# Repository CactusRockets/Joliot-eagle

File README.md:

# Avionics Boards for the Joliot Rocket

This repository contains the design files for the avionics boards used in the **Joliot rocket** developed by **Cactus Rockets Design**.

### Description

The avionics system is composed of the following boards:

* **Processing Board**
* **Actuation Board**
* **Battery Board**

The **Processing Board** is responsible for handling sensor data, data logging, and telemetry transmission.

The **Actuation Board** contains the circuitry required for the correct activation of the *Skib* (the recovery deployment mechanism).

The **Battery Board** distributes the battery voltages to connectors so they can be easily used by the other boards.

*Note:* All board files can be opened using **Autodesk Eagle**.

### Schematics and Layouts

Processing Board:

Actuation Board:

Battery Board:

### Operation

The Processing Board includes a system-activation switch. Once the switch is pressed, the system powers on and begins reading all onboard modules. After each reading, the data is stored on a microSD card and transmitted via telemetry.

When the Processing Board detects a fall event, it sends a signal to the Actuation Board, which then activates the *Skib* to deploy the drogue recovery system.

Na queda do foguete com apenas o paraquedas drogue liberado, no momento que o foguete tiver abaixo de 500m de altitude, o sistema deve detectar isso e ativar o outro skib que aciona o sistema de recuperação principal do foguete, liberando assim o paraquedas main. Fazendo assim que o foguete tenha um voo e recuperação estável até o chão.

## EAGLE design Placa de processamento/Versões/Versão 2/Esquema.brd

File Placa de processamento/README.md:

#### Placas da aviônica do foguete de 1km

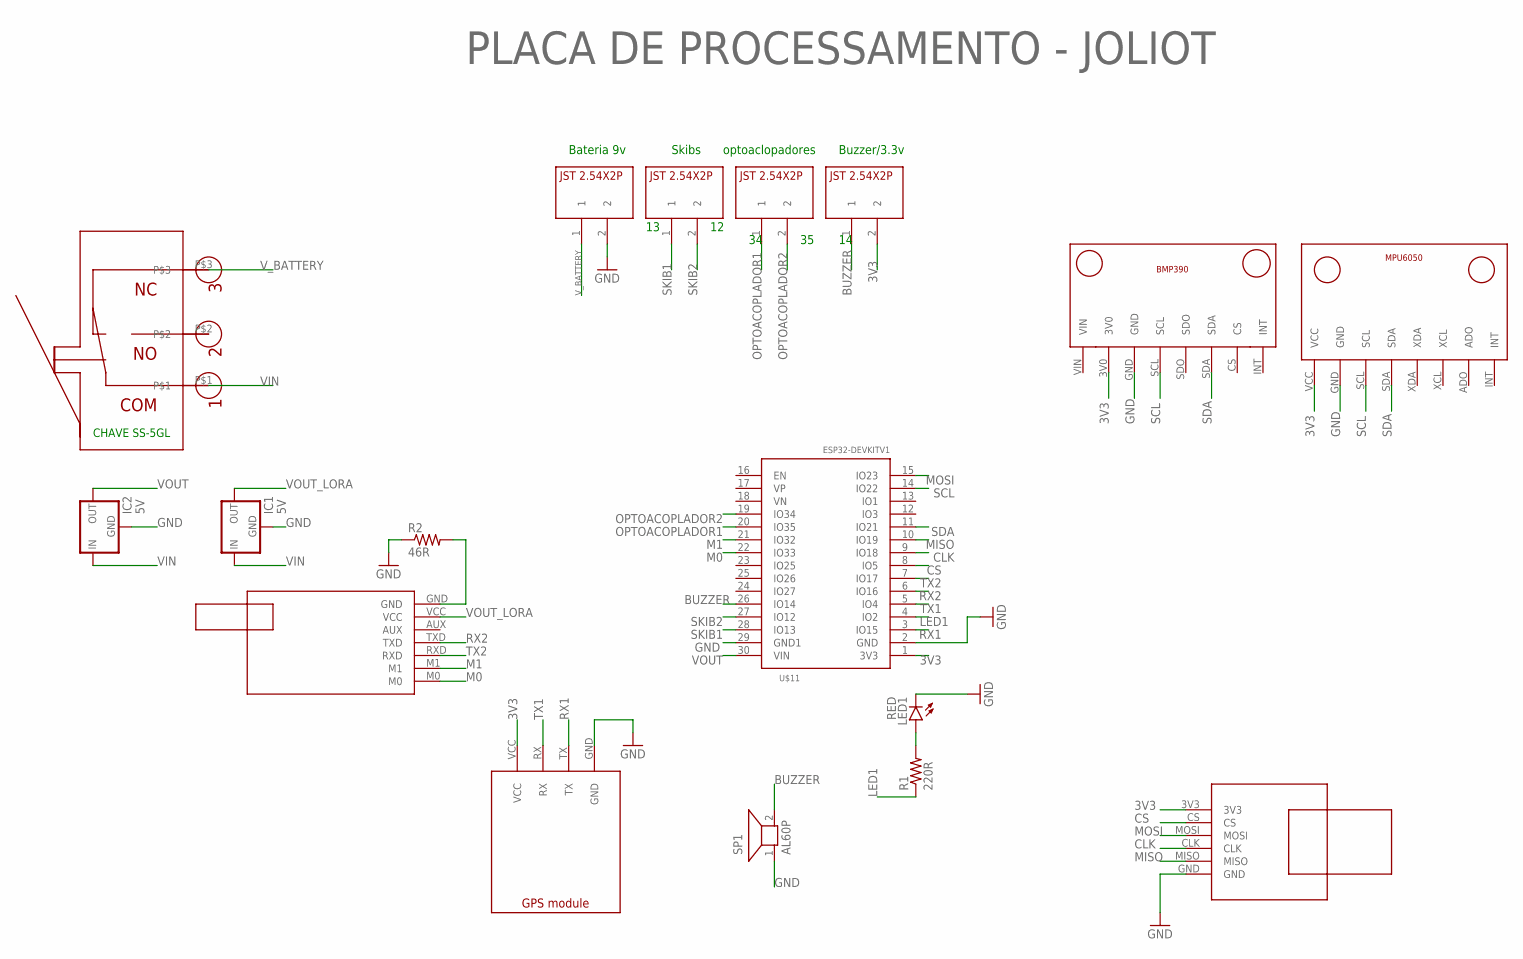
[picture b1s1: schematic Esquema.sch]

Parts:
IC1, IC2: 5V; 78XXL
LED1: RED; LED5MM
R1: 220R; 0309/12
R2: 46R; 0309/12
SP1: AL60P
U$1: BMP390V1; BMP390_FOOTPRINT
U$2: E22-400T30D; E22-400T30D_FOOTPRINT
U$3: GPS_MODULE; GPS_MODULE_FOOTPRINT
U$4, U$5, U$6, U$7: JST2.54X2P; JST2.54X2P_FOOTPRINT
U$8: MICROSD_SMALL_READER; MICROSD_SMALL_READER_FOOTPRINT
U$9: MPU6050V1; MPU6050_FOOTPRINT
U$11: ESP32DEVKITV1; ESP32-DEVKITV1
U$12: CHAVE_SS-5GL; CHAVESS-5GL

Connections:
3V3: U$1.3V0, U$3.VCC, U$4.2, U$8.3V3, U$9.VCC, U$11.1 (3V3)
BUZZER: SP1.2, U$4.1, U$11.26 (IO14)
CLK: U$8.CLK, U$11.9 (IO18)
CS: U$8.CS, U$11.8 (IO5)
GND: IC1.GND, IC2.GND, LED1.K (C), R2.1, SP1.1, U$1.GND, U$3.GND, U$7.2, U$8.GND, U$9.GND, U$11.2 (GND), U$11.29 (GND1)
LED1: R1.1, U$11.4 (IO2)
M0: U$2.M0, U$11.22 (IO33)
M1: U$2.M1, U$11.21 (IO32)
MISO: U$8.MISO, U$11.10 (IO19)
MOSI: U$8.MOSI, U$11.15 (IO23)
unnamed: LED1.A, R1.2
unnamed: R2.2, U$2.GND
OPTOACOPLADOR1: U$5.1, U$11.20 (IO35)
OPTOACOPLADOR2: U$5.2, U$11.19 (IO34)
RX1: U$3.TX, U$11.3 (IO15)
RX2: U$2.TXD, U$11.6 (IO16)
SCL: U$1.SCL, U$9.SCL, U$11.14 (IO22)
SDA: U$1.SDA, U$9.SDA, U$11.11 (IO21)
SKIB1: U$6.1, U$11.28 (IO13)
SKIB2: U$6.2, U$11.27 (IO12)
TX1: U$3.RX, U$11.5 (IO4)
TX2: U$2.RXD, U$11.7 (IO17)
VIN: IC1.IN, IC2.IN, U$12.P$1
VOUT: IC2.OUT, U$11.30 (VIN)
VOUT_LORA: IC1.OUT, U$2.VCC
V_BATTERY: U$7.1, U$12.P$3

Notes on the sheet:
Bateria 9v
Skibs
optoaclopadores
Buzzer/3.3v
PLACA DE PROCESSAMENTO - JOLIOT

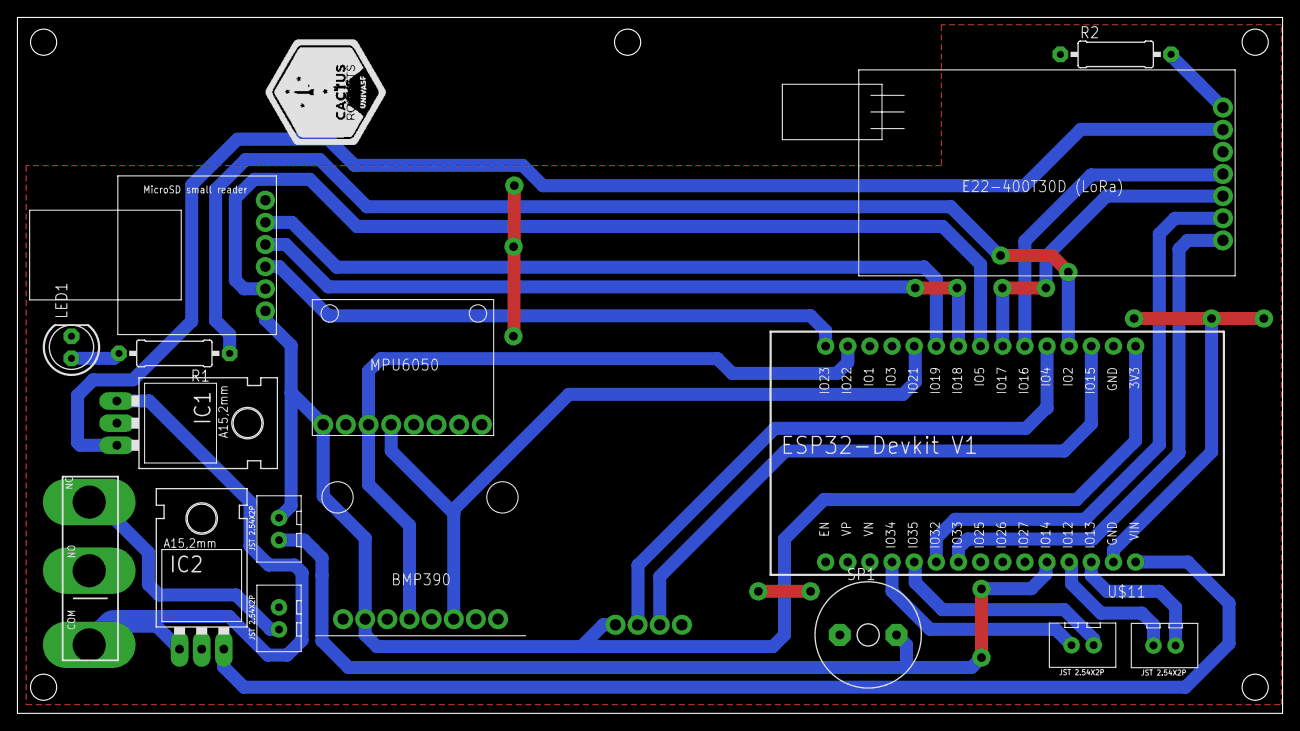
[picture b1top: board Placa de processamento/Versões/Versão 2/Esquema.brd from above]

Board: 2 copper layers, 145.1 x 79.8 mm, 17 parts (1 on the bottom side), 26 nets.

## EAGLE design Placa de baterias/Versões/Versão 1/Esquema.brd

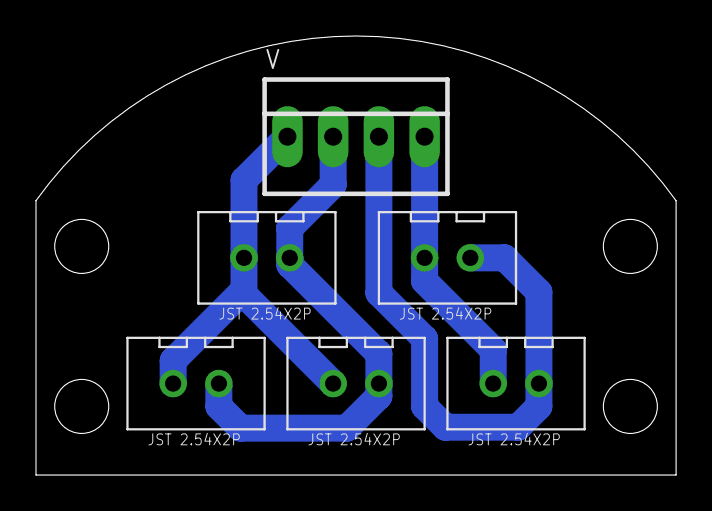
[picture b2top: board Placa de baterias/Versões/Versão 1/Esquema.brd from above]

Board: 2 copper layers, 35.6 x 24.4 mm, 6 parts (0 on the bottom side), 4 nets.

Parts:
U$1, U$2, U$3, U$4, U$5: JST2.54X2P; JST2.54X2P_FOOTPRINT
V: 22-23-2041

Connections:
V1+: U$1.1, U$4.1, V.3
V1-: U$1.2, U$4.2, V.4
V2+: U$2.1, U$3.1, U$5.1, V.2
V2-: U$2.2, U$3.2, U$5.2, V.1

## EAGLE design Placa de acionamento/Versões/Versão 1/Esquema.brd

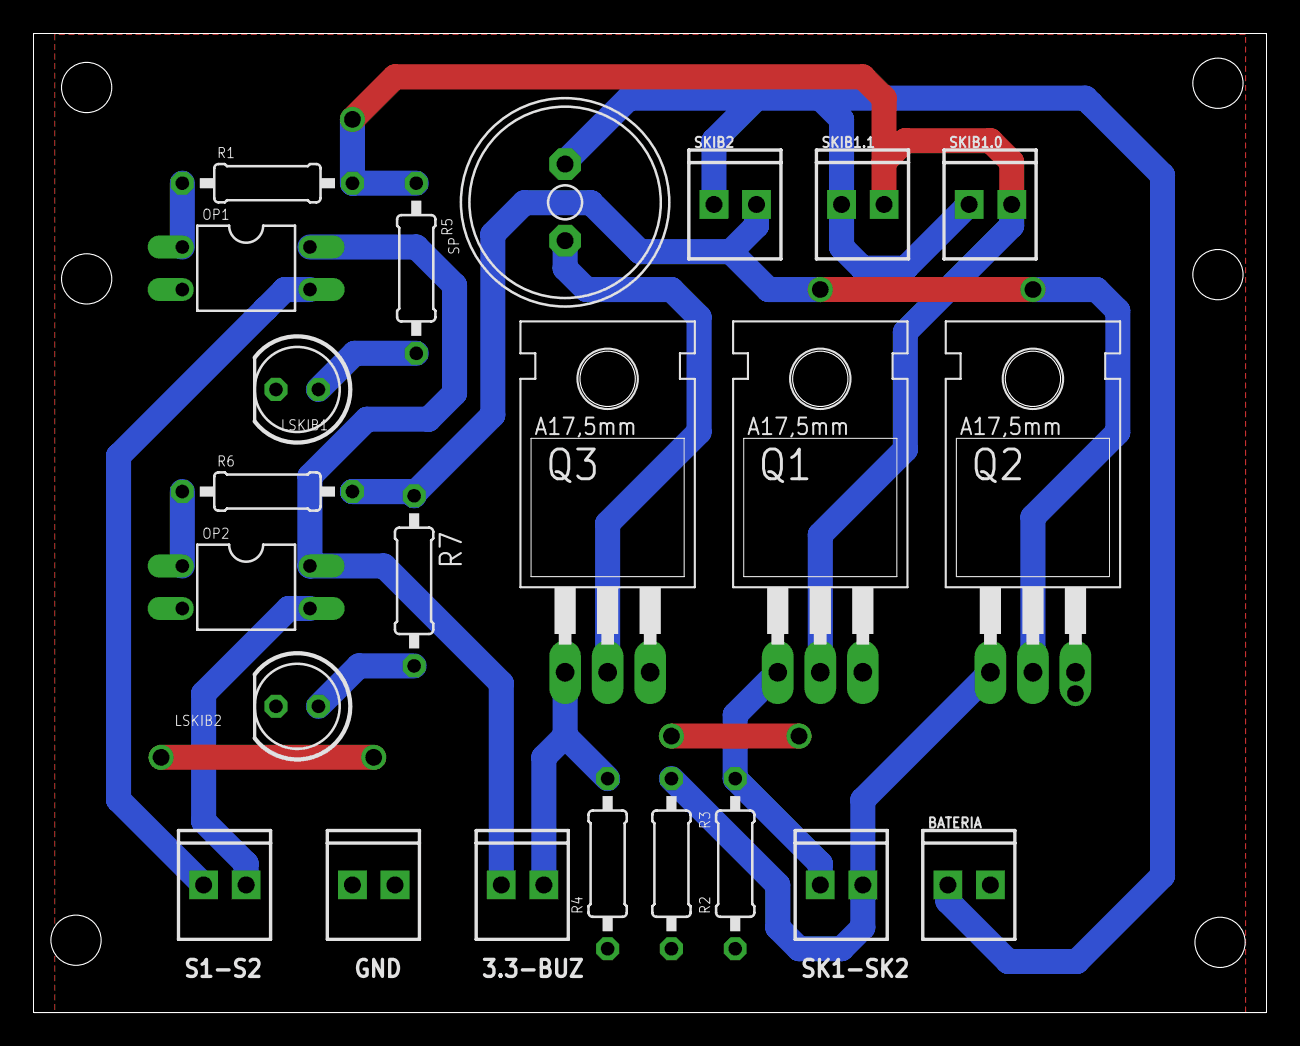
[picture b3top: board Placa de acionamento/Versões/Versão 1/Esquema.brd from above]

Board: 2 copper layers, 73.6 x 58.5 mm, 23 parts (0 on the bottom side), 15 nets.

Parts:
3.3-BUZ: 1X02_2.54_SCREWTERM
BATERIA: 1X02_2.54_SCREWTERM
GND: 1X02_2.54_SCREWTERM
LSKIB1, LSKIB2: 5mm; LED5MM
OP1, OP2: PC817; DIL04
Q1, Q2, Q3: IRF540; TO220
R1, R2, R3, R4, R5, R6, R7: 1k; 0207/10
S1-S2: 1X02_2.54_SCREWTERM
SK1-SK2: 1X02_2.54_SCREWTERM
SKIB1.0, SKIB1.1, SKIB2: 1X02_2.54_SCREWTERM
SP: AL11P

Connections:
3.3V: 3.3-BUZ.P2, OP1.4, OP2.4
BUZZER: 3.3-BUZ.P1, Q3.1, R4.2
GND: BATERIA.P1, GND.P1, GND.P2, LSKIB1.K, LSKIB2.K, OP1.2, OP2.2, Q1.3, Q2.3, Q3.3, R2.1, R3.1, R4.1
unnamed: LSKIB2.A, R7.2
unnamed: Q3.2, SP.-
unnamed: LSKIB1.A, R5.2
unnamed: OP1.1, R1.1
unnamed: OP2.1, R6.1
SINAL_SKIB1: OP1.3, S1-S2.P2
SINAL_SKIB2: OP2.3, S1-S2.P1
SKIB1: Q1.1, R2.2, SK1-SK2.P2
SKIB1_CONECTOR: Q1.2, R1.2, R5.1, SKIB1.0.P1, SKIB1.1.P1
SKIB2: Q2.1, R3.2, SK1-SK2.P1
SKIB2_CONECTOR: Q2.2, R6.2, R7.1, SKIB2.P1
VCC: BATERIA.P2, SKIB1.0.P2, SKIB1.1.P2, SKIB2.P2, SP.+

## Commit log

2024-04-18 Criado projeto 'Placa de acionamento'
2024-04-18 Adicionado conexão LoRa
2024-04-19 Ligado MPU ao ESP32
2024-04-19 Adicionado quase totas as conexões, falta aquelas relacionadas à alimentação (conectores JST)
2024-04-20 Placa de acionamento
2024-04-20 Upload para o Fusion
2024-04-21 Update de roteamento
2024-04-21 Roteamento da placa
2024-04-21 Componentes de biblioteca atualizados
2024-04-22 Ajuste nas conexões e trilhas
2024-04-22 Ajustado furos e trilhas
2024-04-22 Ajustes em trilhas, adicionado furos, ajustado dimensões
2024-04-22 Ajuste de trilhas, furos e posicionamento.
2024-04-22 Ajustes na PCB finalizados!
2024-04-22 Finalizados os ajustes na placa de acionamento do Joliot.
2024-04-22 Finalizado!
2024-04-22 Ajustes finalizados!
2024-04-23 Adicionado plano de terra no top - Joliot processamento.
2024-04-23 Atualização
2024-04-23 Adicionado LED indicativo.
2024-11-06 placa de baterias
2024-11-19 Adiciona Placa de processamento ao repositório
2024-11-27 Coisas
2025-02-18 mudanças na placa de processamento
2025-07-01 atualização placa de baterias
2025-07-29 teste
2025-08-26 atualização de regulador
2025-08-30 FEAT: Regulador de tensão do LoRa adicionado
2025-09-01 CHORE: adicionando modelos 3D
2025-09-01 resolved erros in pcb layout
2025-09-01 uptate boards
2025-09-01 resolved layout position
2025-09-02 CHORE: atualizando modelos 3D
2025-09-04 update position
2026-01-14 Update recovery system description in README
    Added details about the drogue recovery system and main parachute activation.

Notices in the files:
parts and their libraries:
SparkFun-Connectors: Licensing: Creative Commons ShareAlike 4.0 International - https://creativecommons.org/licenses/by-sa/4.0
